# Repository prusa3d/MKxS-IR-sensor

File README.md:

# PRUSA IR sensor board

KiCad PCB layout

* [Interactive bom](http://htmlpreview.github.io/?https://github.com/prusa3d/MKxS-IR-sensor/blob/master/rev.041/IR-endstop-0.4.1-ibom.html)
* [STEP 3D model](rev.041/IR-endstop-0.4.1.step)

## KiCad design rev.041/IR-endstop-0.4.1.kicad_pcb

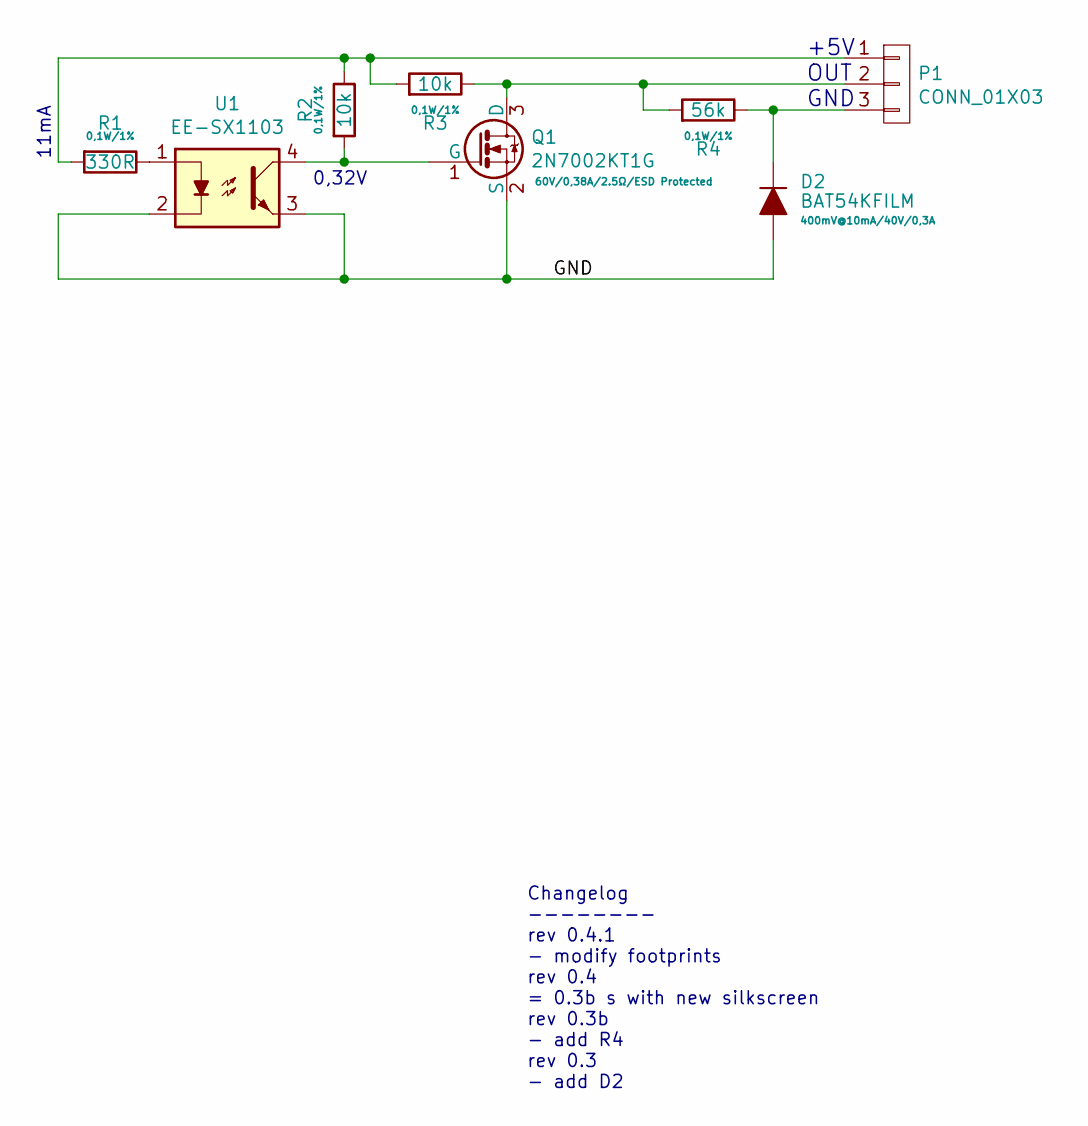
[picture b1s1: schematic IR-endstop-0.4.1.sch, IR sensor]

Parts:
D2: BAT54KFILM; SOD-523-ShortSilk
P1: CONN_01X03; Pin_Header_Angled_1x03
Q1: 2N7002KT1G; SOT-23
R1: 330R; R_0603
R2, R3: 10k; R_0402
R4: 56k; R_0402
U1: EE-SX1103; IR-EE-SX1103

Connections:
/GND: D2.2 (A), Q1.2 (S), U1.2, U1.3
unnamed: D2.1 (K), P1.3, R4.1
unnamed: P1.1, R1.2, R2.1, R3.2
unnamed: P1.2, Q1.3 (D), R3.1, R4.2
unnamed: Q1.1 (G), R2.2, U1.4
unnamed: R1.1, U1.1

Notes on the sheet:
+5V OUT GND
11mA
0,32V
Changelog -------- rev 0.4.1 - modify footprints rev 0.4 = 0.3b s with new silkscreen rev 0.3b - add R4 rev 0.3 - add D2

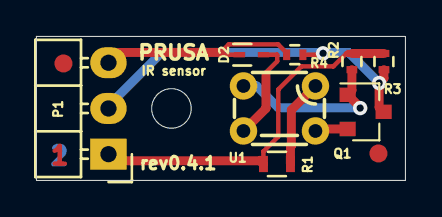
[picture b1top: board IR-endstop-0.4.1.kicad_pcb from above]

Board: 2 copper layers, 20.5 x 8.0 mm, 8 parts (0 on the bottom side), 6 nets.

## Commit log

2020-04-27 pcb rev0.4
2021-01-12 0.4.1

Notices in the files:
rev.041/IR-endstop-0.4.1.kicad_pcb:
Licensed under the Attribution-ShareAlike 4.0 International (CC BY-SA 4.0)
rev.041/IR-endstop-0.4.1.sch:
http://creativecommons.org/licenses/by-sa/4.0
